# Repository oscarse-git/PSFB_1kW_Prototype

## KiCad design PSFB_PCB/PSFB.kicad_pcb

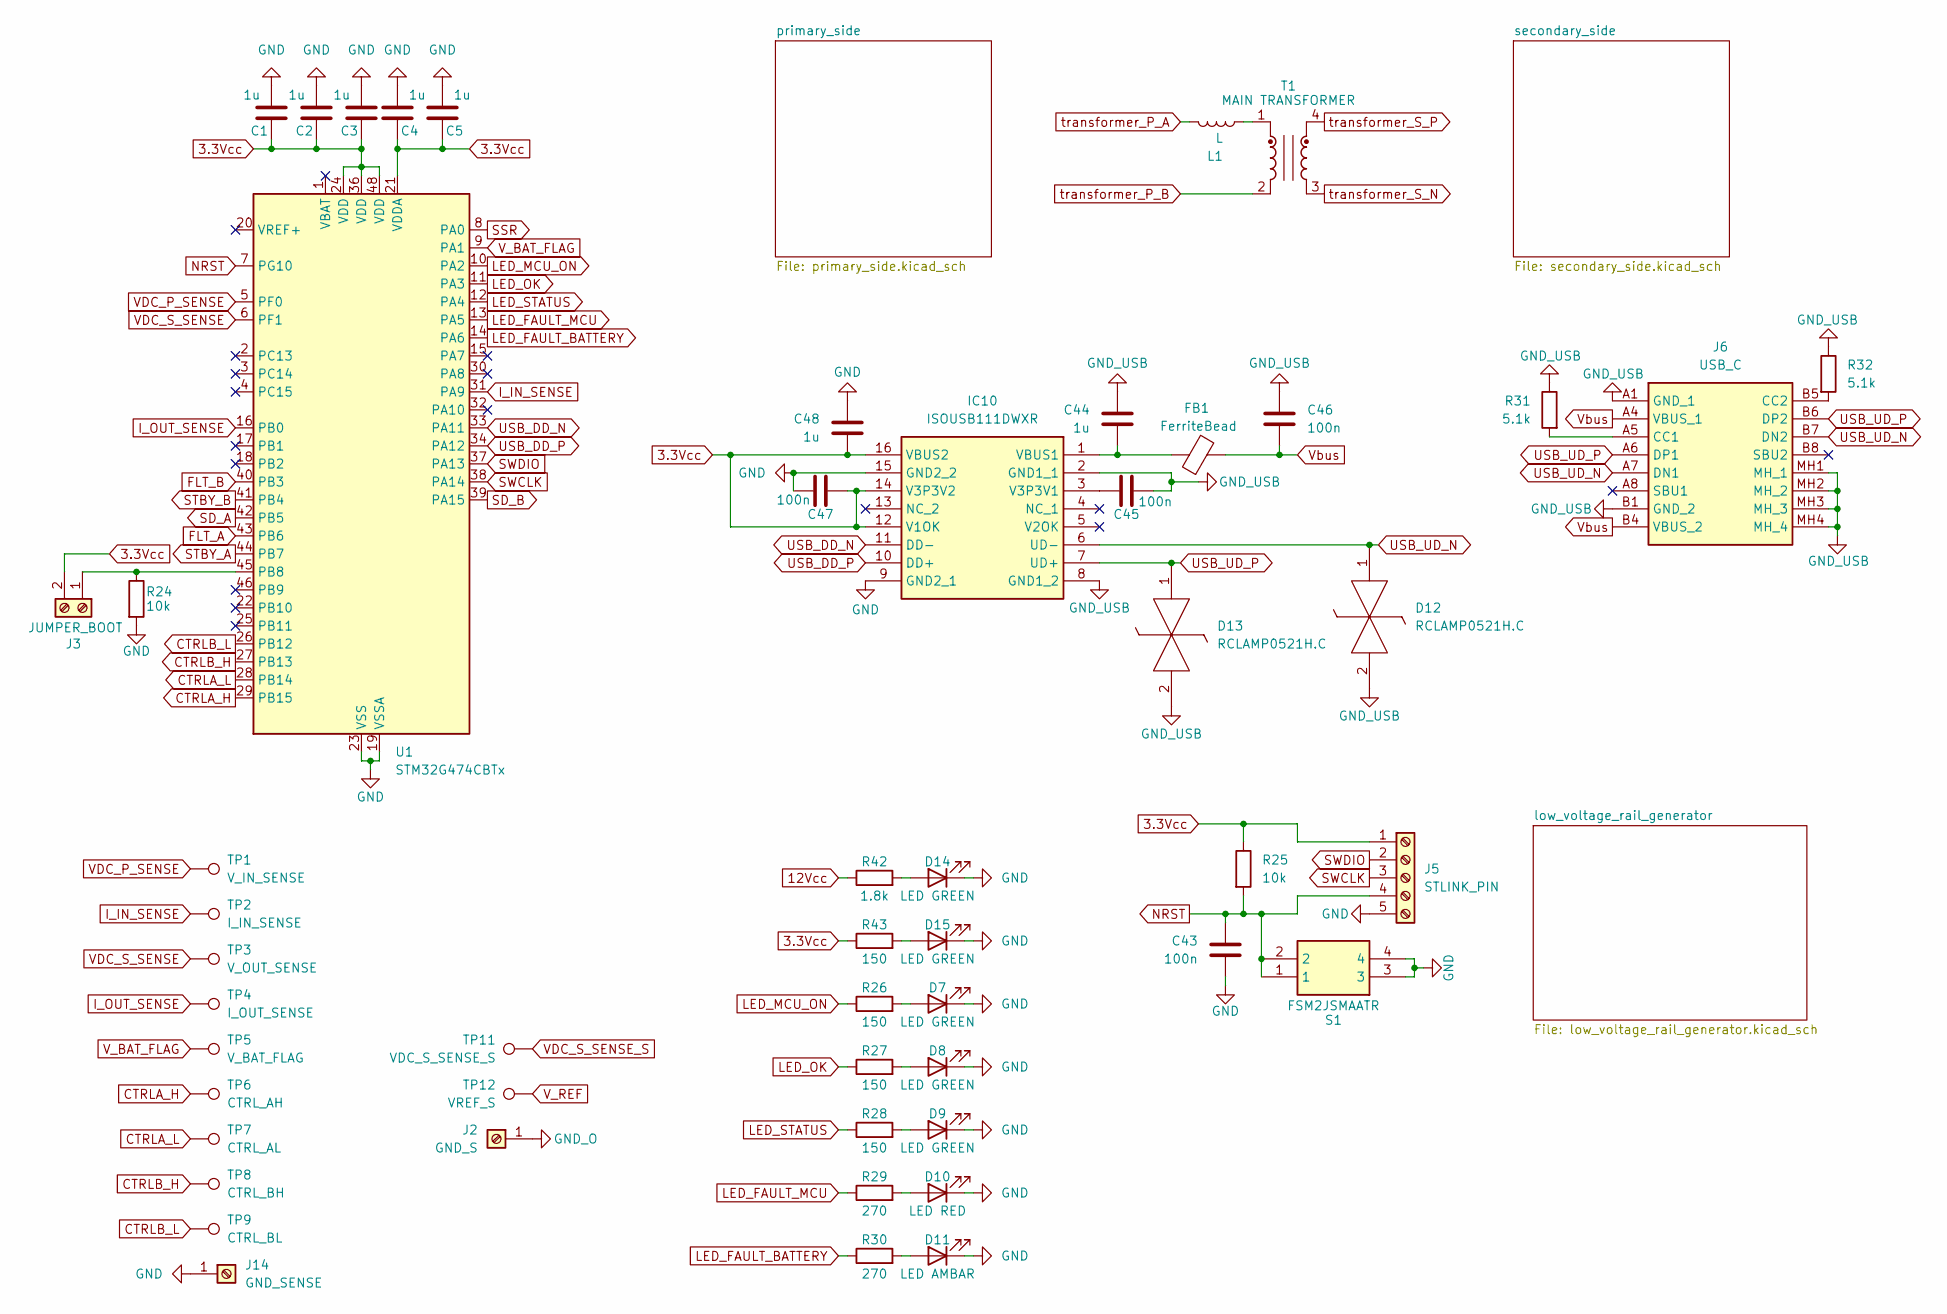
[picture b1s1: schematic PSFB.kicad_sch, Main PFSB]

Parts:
C1, C2, C3, C4, C5: 1u; C_0603_1608Metric_Pad1.08x0.95mm_HandSolder
C43, C45, C46, C47: 100n; C_1206_3216Metric_Pad1.33x1.80mm_HandSolder
C44, C48: 1u; C_1206_3216Metric
D7, D8, D9, D14, D15: LED GREEN; LED_0603_1608Metric
D10: LED RED; LED_1206_3216Metric_Pad1.42x1.75mm_HandSolder
D11: LED AMBAR; LED_1206_3216Metric_Pad1.42x1.75mm_HandSolder
D12, D13: RCLAMP0521H.C; SOD2513X120N; Mouser Part Number 947-RCLAMP0521H.C
FB1: FerriteBead; R_0603_1608Metric_Pad0.98x0.95mm_HandSolder
IC10: ISOUSB111DWXR; SOP65P1030X260-16N; Mouser Part Number 595-ISOUSB111DWXR
J2: GND_S; PinHeader_1x01_P2.54mm_Vertical
J3: JUMPER_BOOT; PinHeader_1x02_P2.54mm_Vertical
J5: STLINK_PIN; PinHeader_1x05_P2.54mm_Vertical
J6: USB_C; UJ20CHGMSMT4BP16TR; Manufacturer_Part_Number UJ20-C-H-G-MSMT-4B-P16-TR
J14: GND_SENSE; PinHeader_1x01_P2.54mm_Vertical
L1: L; L_Wurth_WE-HCFT-2012_LeadDiameter1.5mm
R24, R25: 10k; R_0603_1608Metric_Pad0.98x0.95mm_HandSolder
R26, R27, R28, R43: 150; R_0603_1608Metric_Pad0.98x0.95mm_HandSolder
R29, R30: 270; R_0603_1608Metric_Pad0.98x0.95mm_HandSolder
R31, R32: 5.1k; R_0603_1608Metric_Pad0.98x0.95mm_HandSolder
R42: 1.8k; R_0603_1608Metric_Pad0.98x0.95mm_HandSolder
S1: FSM2JSMAATR; FSM2J_1; Mouser Part Number 506-FSM2JSMAATR
T1: MAIN TRANSFORMER; TRANSFORMER_PQ_PSFB
TP1: V_IN_SENSE; TestPoint_Pad_D1.0mm
TP2: I_IN_SENSE; TestPoint_Pad_D1.0mm
TP3: V_OUT_SENSE; TestPoint_Pad_D1.0mm
TP4: I_OUT_SENSE; TestPoint_Pad_D1.0mm
TP5: V_BAT_FLAG; TestPoint_Pad_D1.0mm
TP6: CTRL_AH; TestPoint_Pad_D1.0mm
TP7: CTRL_AL; TestPoint_Pad_D1.0mm
TP8: CTRL_BH; TestPoint_Pad_D1.0mm
TP9: CTRL_BL; TestPoint_Pad_D1.0mm
TP11: VDC_S_SENSE_S; TestPoint_Pad_D1.0mm
TP12: VREF_S; TestPoint_Pad_D1.0mm
U1: STM32G474CBTx; LQFP-48_7x7mm_P0.5mm

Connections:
3.3Vcc: C1.1, C2.1, C3.1, C4.1, C5.1, C47.2, C48.2, IC10.12 (V1OK), IC10.14 (V3P3V2), IC10.16 (VBUS2), J3.2, J5.1, R25.1, R43.1, U1.21 (VDDA), U1.24 (VDD), U1.36 (VDD), U1.48 (VDD); also elsewhere on the board
12Vcc: R42.1; also elsewhere on the board
CTRLA_H: TP6.1, U1.29 (PB15); also elsewhere on the board
CTRLA_L: TP7.1, U1.28 (PB14); also elsewhere on the board
CTRLB_H: TP8.1, U1.27 (PB13); also elsewhere on the board
CTRLB_L: TP9.1, U1.26 (PB12); also elsewhere on the board
FLT_A: U1.43 (PB6); also elsewhere on the board
FLT_B: U1.40 (PB3); also elsewhere on the board
GND: C1.2, C2.2, C3.2, C4.2, C5.2, C43.2, C47.1, C48.1, D7.1 (K), D8.1 (K), D9.1 (K), D10.1 (K), D11.1 (K), D14.1 (K), D15.1 (K), IC10.9 (GND2_1), IC10.15 (GND2_2), J5.5, J14.1, R24.2, S1.3, S1.4, U1.19 (VSSA), U1.23 (VSS), U1.35 (VSS), U1.47 (VSS); also elsewhere on the board
GND_O: J2.1; also elsewhere on the board
GND_USB: C44.1, C45.1, C46.1, D12.2, D13.2, IC10.2 (GND1_1), IC10.8 (GND1_2), J6.A1 (GND_1), J6.B1 (GND_2), J6.MH1 (MH_1), J6.MH2 (MH_2), J6.MH3 (MH_3), J6.MH4 (MH_4), R31.1, R32.1
I_IN_SENSE: TP2.1, U1.31 (PA9); also elsewhere on the board
I_OUT_SENSE: TP4.1, U1.16 (PB0); also elsewhere on the board
LED_FAULT_BATTERY: R30.1, U1.14 (PA6)
LED_FAULT_MCU: R29.1, U1.13 (PA5)
LED_MCU_ON: R26.1, U1.10 (PA2)
LED_OK: R27.1, U1.11 (PA3)
LED_STATUS: R28.1, U1.12 (PA4)
NRST: C43.1, J5.4, R25.2, S1.1, S1.2, U1.7 (PG10)
unnamed: D7.2 (A), R26.2
unnamed: D8.2 (A), R27.2
unnamed: D9.2 (A), R28.2
unnamed: D10.2 (A), R29.2
unnamed: D11.2 (A), R30.2
unnamed: D14.2 (A), R42.2
unnamed: D15.2 (A), R43.2
unnamed: C45.2, IC10.3 (V3P3V1)
unnamed: C44.2, FB1.1, IC10.1 (VBUS1)
unnamed: J3.1, R24.1, U1.45 (PB8)
unnamed: J6.A5 (CC1), R31.2
unnamed: J6.B5 (CC2), R32.2
unnamed: L1.2, T1.1
SD_A: U1.42 (PB5); also elsewhere on the board
SD_B: U1.39 (PA15); also elsewhere on the board
SSR: U1.8 (PA0); also elsewhere on the board
STBY_A: U1.44 (PB7); also elsewhere on the board
STBY_B: U1.41 (PB4); also elsewhere on the board
SWCLK: J5.3, U1.38 (PA14)
SWDIO: J5.2, U1.37 (PA13)
USB_DD_N: IC10.11 (DD-), U1.33 (PA11)
USB_DD_P: IC10.10 (DD+), U1.34 (PA12)
USB_UD_N: D12.1, IC10.6 (UD-), J6.A7 (DN1), J6.B7 (DN2)
USB_UD_P: D13.1, IC10.7 (UD+), J6.A6 (DP1), J6.B6 (DP2)
VDC_P_SENSE: TP1.1, U1.5 (PF0); also elsewhere on the board
VDC_S_SENSE: TP3.1, U1.6 (PF1); also elsewhere on the board
VDC_S_SENSE_S: TP11.1; also elsewhere on the board
V_BAT_FLAG: TP5.1, U1.9 (PA1); also elsewhere on the board
V_REF: TP12.1; also elsewhere on the board
Vbus: C46.2, FB1.2, J6.A4 (VBUS_1), J6.B4 (VBUS_2)
transformer_P_A: L1.1; also elsewhere on the board
transformer_P_B: T1.2; also elsewhere on the board
transformer_S_N: T1.3; also elsewhere on the board
transformer_S_P: T1.4; also elsewhere on the board

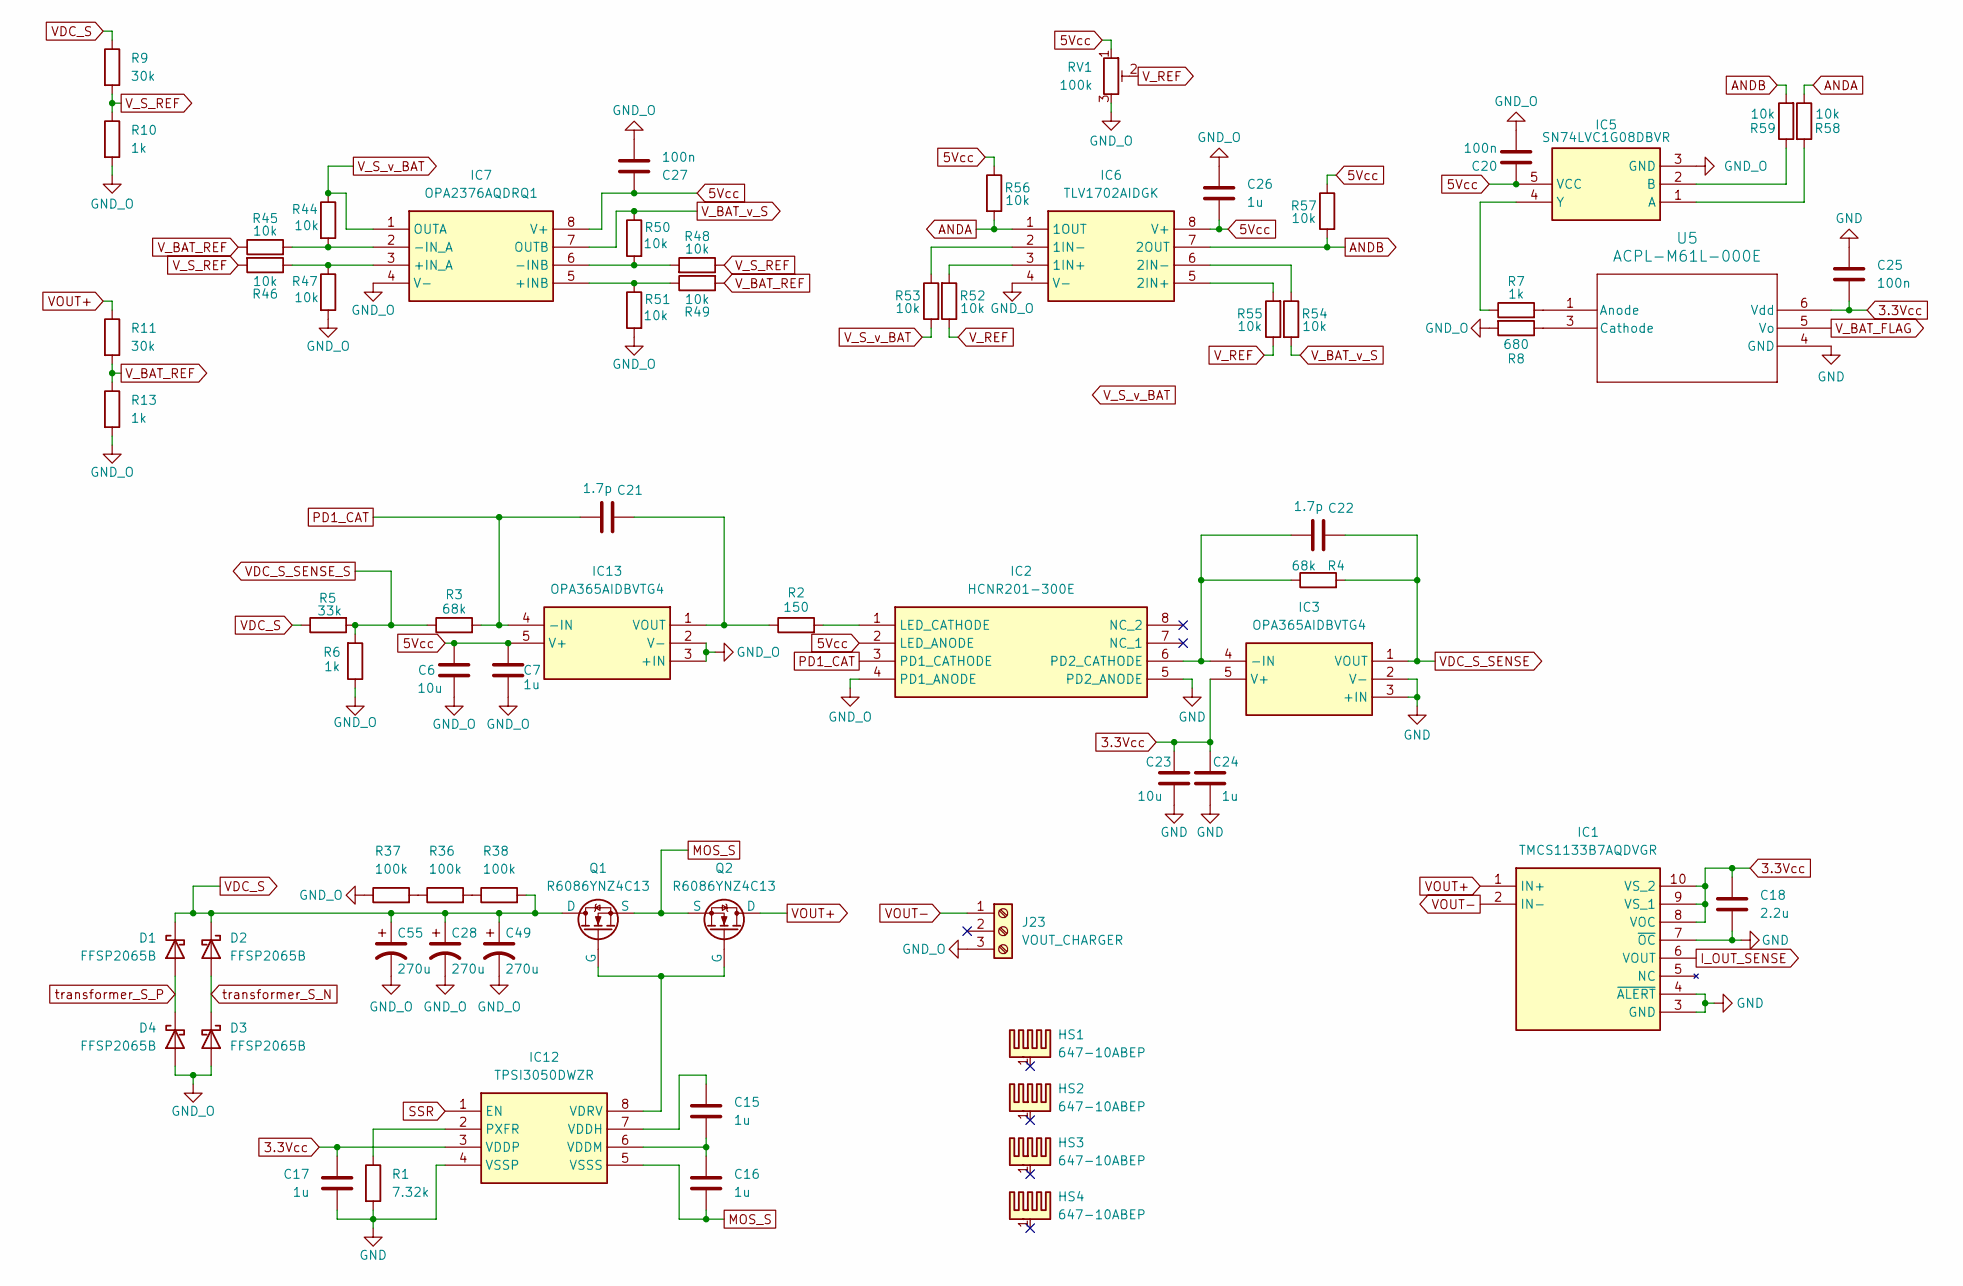
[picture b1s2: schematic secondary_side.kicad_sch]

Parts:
C6, C23: 10u; C_1206_3216Metric
C7, C15, C16, C17, C24, C26: 1u; C_1206_3216Metric
C18: 2.2u; C_0603_1608Metric_Pad1.08x0.95mm_HandSolder
C20, C25, C27: 100n; C_1206_3216Metric_Pad1.33x1.80mm_HandSolder
C21, C22: 1.7p; C_0603_1608Metric_Pad1.08x0.95mm_HandSolder
C28, C49, C55: 270u; CP_Radial_D25.0mm_P10.00mm_SnapIn
D1, D2, D3, D4: FFSP2065B; TO-220-2_Vertical
HS1, HS2, HS3, HS4: 647-10ABEP; XSD-C4649_TO220_Heatsink
IC1: TMCS1133B7AQDVGR; Manufacturer_Part_Number TMCS1133B7AQDVGR
IC2: HCNR201-300E; HCNR201300E; Mouser Part Number 630-HCNR201-300E
IC3, IC13: OPA365AIDBVTG4; SOT95P280X145-5N; Mouser Part Number 595-OPA365AIDBVTG4
IC5: SN74LVC1G08DBVR; SOT95P280X145-5N; Mouser Part Number 595-SN74LVC1G08DBVR
IC6: TLV1702AIDGK; SOP65P490X110-8N; Mouser Part Number 595-TLV1702AIDGK
IC7: OPA2376AQDRQ1; SOIC127P600X175-8N; Mouser Part Number 595-OPA2376AQDRQ1
IC12: TPSI3050DWZR; SOIC127P1150X280-8N; Mouser Part Number 595-TPSI3050DWZR
J23: VOUT_CHARGER; 1731734
Q1, Q2: R6086YNZ4C13; TO-247-3_Vertical
R1: 7.32k; R_0603_1608Metric_Pad0.98x0.95mm_HandSolder
R2: 150; R_0805_2012Metric_Pad1.20x1.40mm_HandSolder
R3, R4: 68k; R_0805_2012Metric_Pad1.20x1.40mm_HandSolder
R5: 33k; R_0603_1608Metric_Pad0.98x0.95mm_HandSolder
R6, R7, R10, R13: 1k; R_0603_1608Metric_Pad0.98x0.95mm_HandSolder
R8: 680; R_0603_1608Metric_Pad0.98x0.95mm_HandSolder
R9, R11: 30k; R_0603_1608Metric_Pad0.98x0.95mm_HandSolder
R36, R37, R38: 100k; R_1206_3216Metric_Pad1.30x1.75mm_HandSolder
R44, R45, R46, R47, R48, R49, R50, R51, R52, R53, R54, R55, R56, R57, R58, R59: 10k; R_0603_1608Metric_Pad0.98x0.95mm_HandSolder
RV1: 100k; PVG3A104C01R00
U5: ACPL-M61L-000E; SO-5_AVA-L

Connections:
3.3Vcc: C17.1, C18.1, C23.1, C24.1, C25.2, IC1.8 (VOC), IC1.9 (VS_1), IC1.10 (VS_2), IC3.5 (V+), IC12.3 (VDDP), U5.6 (Vdd); also elsewhere on the board
5Vcc: C6.1, C7.1, C20.1, C26.2, C27.1, IC2.2 (LED_ANODE), IC5.5 (VCC), IC6.8 (V+), IC7.8 (V+), IC13.5 (V+), R56.1, R57.1, RV1.1; also elsewhere on the board
ANDA: IC6.1 (1OUT), R56.2, R58.1
ANDB: IC6.7 (2OUT), R57.2, R59.2
GND: C17.2, C18.2, C23.2, C24.2, C25.1, IC1.3 (GND), IC1.4 (~ALERT), IC1.7 (~OC), IC2.5 (PD2_ANODE), IC3.2 (V-), IC3.3 (+IN), IC12.4 (VSSP), R1.2, U5.4 (GND); also elsewhere on the board
GND_O: C6.2, C7.2, C20.2, C26.1, C27.2, C28.2, C49.2, C55.2, D3.2 (A), D4.2 (A), IC2.4 (PD1_ANODE), IC5.3 (GND), IC6.4 (V-), IC7.4 (V-), IC13.2 (V-), IC13.3 (+IN), J23.3, R6.1, R8.2, R10.2, R13.2, R37.1, R47.2, R51.2, RV1.3; also elsewhere on the board
I_OUT_SENSE: IC1.6 (VOUT); also elsewhere on the board
MOS_S: C16.2, IC12.5 (VSSS), Q1.3 (S), Q2.3 (S)
unnamed: IC2.1 (LED_CATHODE), R2.2
unnamed: C22.2, IC2.6 (PD2_CATHODE), IC3.4 (-IN), R4.1
unnamed: IC5.1 (A), R58.2
unnamed: IC5.2 (B), R59.1
unnamed: IC5.4 (Y), R7.1
unnamed: IC6.3 (1IN+), R52.2
unnamed: IC6.2 (1IN-), R53.1
unnamed: IC6.5 (2IN+), R55.2
unnamed: IC6.6 (2IN-), R54.1
unnamed: IC7.5 (+INB), R49.1, R51.1
unnamed: IC7.3 (+IN_A), R46.1, R47.1
unnamed: IC7.6 (-INB), R48.2, R50.2
unnamed: IC7.2 (-IN_A), R44.2, R45.2
unnamed: IC12.2 (PXFR), R1.1
unnamed: C15.1, IC12.7 (VDDH)
unnamed: C15.2, C16.1, IC12.6 (VDDM)
unnamed: IC12.8 (VDRV), Q1.2 (G), Q2.2 (G)
unnamed: C21.1, IC13.1 (VOUT), R2.1
unnamed: R36.1, R37.2
unnamed: R36.2, R38.1
unnamed: R7.2, U5.1 (Anode)
unnamed: R8.1, U5.3 (Cathode)
PD1_CAT: C21.2, IC2.3 (PD1_CATHODE), IC13.4 (-IN), R3.2
SSR: IC12.1 (EN); also elsewhere on the board
VDC_S: C28.1, C49.1, C55.1, D1.1 (K), D2.1 (K), Q1.1 (D), R5.1, R9.1, R38.2
VDC_S_SENSE: C22.1, IC3.1 (VOUT), R4.2; also elsewhere on the board
VDC_S_SENSE_S: R3.1, R5.2, R6.2; also elsewhere on the board
VOUT+: IC1.1 (IN+), Q2.1 (D), R11.1
VOUT-: IC1.2 (IN-), J23.1
V_BAT_FLAG: U5.5 (Vo); also elsewhere on the board
V_BAT_REF: R11.2, R13.1, R45.1, R49.2
V_BAT_v_S: IC7.7 (OUTB), R50.1, R54.2
V_REF: R52.1, R55.1, RV1.2; also elsewhere on the board
V_S_REF: R9.2, R10.1, R46.2, R48.1
V_S_v_BAT: IC7.1 (OUTA), R44.1, R53.2
transformer_S_N: D2.2 (A), D3.1 (K); also elsewhere on the board
transformer_S_P: D1.2 (A), D4.1 (K); also elsewhere on the board

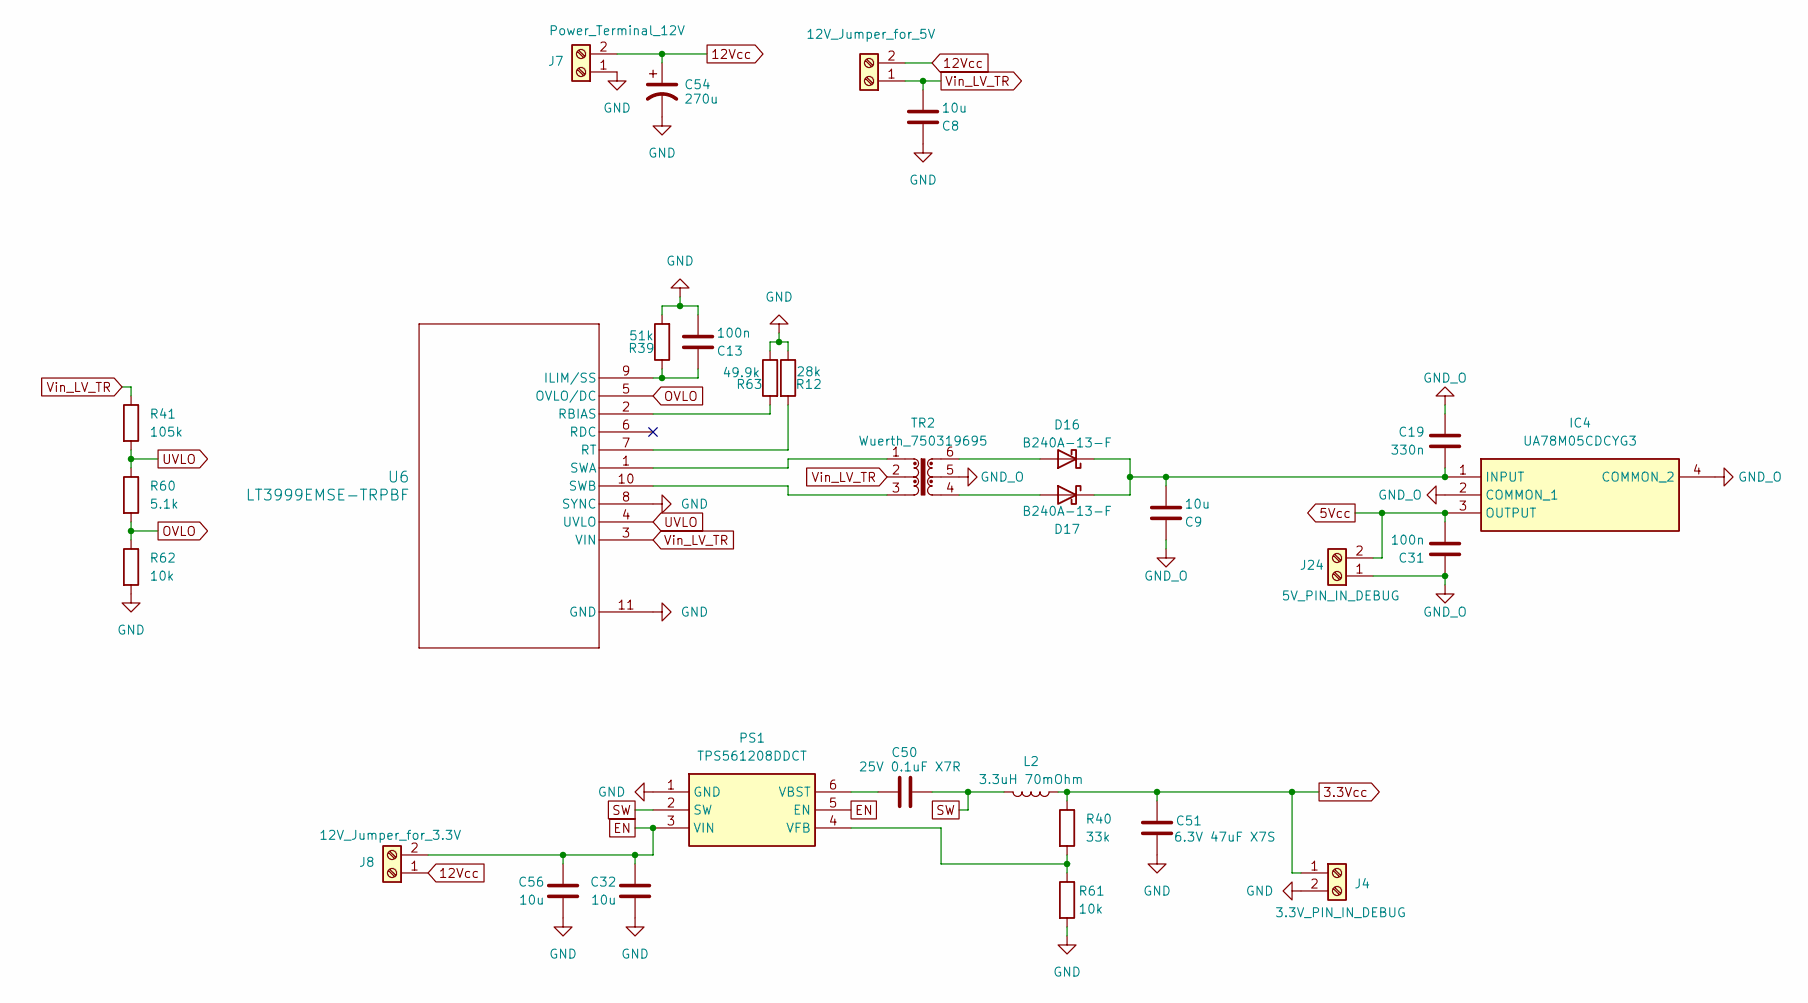
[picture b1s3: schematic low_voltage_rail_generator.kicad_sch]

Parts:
C8, C9, C32, C56: 10u; C_1206_3216Metric
C13, C31: 100n; C_1206_3216Metric_Pad1.33x1.80mm_HandSolder
C19: 330n; C_1206_3216Metric_Pad1.33x1.80mm_HandSolder
C50: 25V 0.1uF X7R; C_0805_2012Metric_Pad1.18x1.45mm_HandSolder
C51: 6.3V 47uF X7S; C_1210_3225Metric_Pad1.33x2.70mm_HandSolder
C54: 270u; CP_Radial_D25.0mm_P10.00mm_SnapIn
D16, D17: B240A-13-F; D_SMA
IC4: UA78M05CDCYG3; SOT230P700X180-4N; Mouser Part Number 595-UA78M05CDCYG3
J1: 12V_Jumper_for_5V; PinHeader_1x02_P2.54mm_Vertical
J4: 3.3V_PIN_IN_DEBUG; PinHeader_1x02_P2.54mm_Vertical
J7: Power_Terminal_12V; 15465512
J8: 12V_Jumper_for_3.3V; PinHeader_1x02_P2.54mm_Vertical
J24: 5V_PIN_IN_DEBUG; PinHeader_1x02_P2.54mm_Vertical
L2: 3.3uH 70mOhm; 784777033
PS1: TPS561208DDCT; SOT95P280X110-6N; Mouser Part Number 595-TPS561208DDCT
R12: 28k; R_0603_1608Metric_Pad0.98x0.95mm_HandSolder
R39: 51k; R_1206_3216Metric_Pad1.30x1.75mm_HandSolder
R40: 33k; R_0603_1608Metric_Pad0.98x0.95mm_HandSolder
R41: 105k; R_1206_3216Metric_Pad1.30x1.75mm_HandSolder
R60: 5.1k; R_1206_3216Metric_Pad1.30x1.75mm_HandSolder
R61: 10k; R_0603_1608Metric_Pad0.98x0.95mm_HandSolder
R62: 10k; R_1206_3216Metric_Pad1.30x1.75mm_HandSolder
R63: 49.9k; R_0603_1608Metric_Pad0.98x0.95mm_HandSolder
TR2: Wuerth_750319695; 750319690
U6: LT3999EMSE-TRPBF; MSOP-10_MSE_LIT-L

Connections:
3.3Vcc: C51.1, J4.1, L2.1, R40.1; also elsewhere on the board
5Vcc: C31.2, IC4.3 (OUTPUT), J24.2; also elsewhere on the board
12Vcc: C54.1, J1.2, J7.2, J8.1; also elsewhere on the board
EN: C32.1, C56.1, J8.2, PS1.3 (VIN), PS1.5 (EN)
GND: C8.1, C13.2, C32.2, C51.2, C54.2, C56.2, J4.2, J7.1, PS1.1 (GND), R12.1, R39.2, R61.2, R62.2, R63.1, U6.8 (SYNC), U6.11 (GND); also elsewhere on the board
GND_O: C9.1, C19.1, C31.1, IC4.2 (COMMON_1), IC4.4 (COMMON_2), J24.1, TR2.5; also elsewhere on the board
unnamed: D16.2 (A), TR2.6
unnamed: C9.2, C19.2, D16.1 (K), D17.1 (K), IC4.1 (INPUT)
unnamed: D17.2 (A), TR2.4
unnamed: C50.2, PS1.6 (VBST)
unnamed: PS1.4 (VFB), R40.2, R61.1
unnamed: C13.1, R39.1, U6.9 (ILIM/SS)
unnamed: R63.2, U6.2 (RBIAS)
unnamed: R12.2, U6.7 (RT)
unnamed: TR2.1, U6.1 (SWA)
unnamed: TR2.3, U6.10 (SWB)
OVLO: R60.2, R62.1, U6.5 (OVLO/DC)
SW: C50.1, L2.2, PS1.2 (SW)
UVLO: R41.2, R60.1, U6.4 (UVLO)
Vin_LV_TR: C8.2, J1.1, R41.1, TR2.2, U6.3 (VIN)

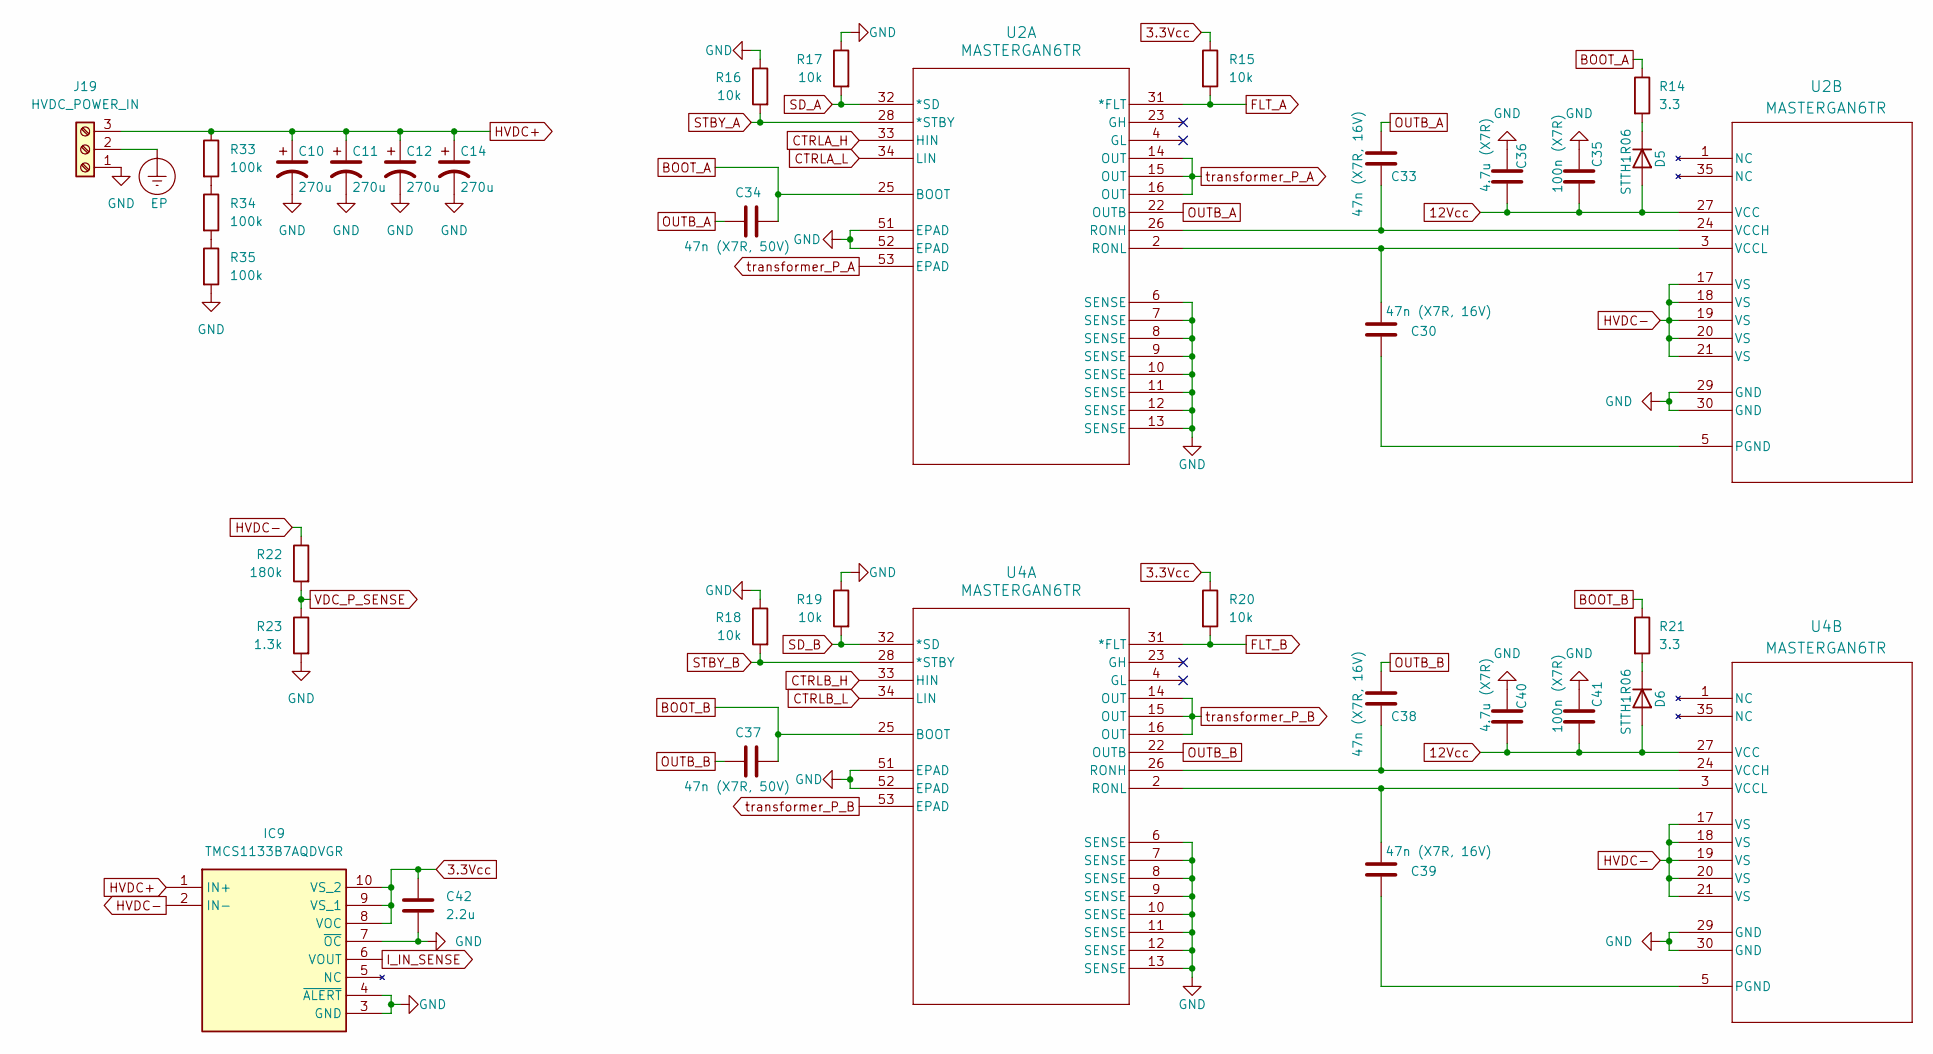
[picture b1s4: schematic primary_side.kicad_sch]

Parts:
C10, C11, C12, C14: 270u; CP_Radial_D25.0mm_P10.00mm_SnapIn
C30, C33, C38, C39: 47n (X7R, 16V); C_0402_1005Metric
C34, C37: 47n (X7R, 50V); C_0603_1608Metric
C35, C41: 100n (X7R); C_0603_1608Metric_Pad1.08x0.95mm_HandSolder
C36, C40: 4.7u (X7R); C_1206_3216Metric_Pad1.33x1.80mm_HandSolder
C42: 2.2u; C_0603_1608Metric_Pad1.08x0.95mm_HandSolder
D5, D6: STTH1R06; DIOM5126X265N
IC9: TMCS1133B7AQDVGR; Manufacturer_Part_Number TMCS1133B7AQDVGR
J19: HVDC_POWER_IN; 1731734
R14, R21: 3.3; R_0805_2012Metric_Pad1.20x1.40mm_HandSolder
R15, R16, R17, R18, R19, R20: 10k; R_0603_1608Metric_Pad0.98x0.95mm_HandSolder
R22: 180k; R_1206_3216Metric_Pad1.30x1.75mm_HandSolder
R23: 1.3k; R_1206_3216Metric_Pad1.30x1.75mm_HandSolder
R33, R34, R35: 100k; R_1206_3216Metric_Pad1.30x1.75mm_HandSolder
U2, U4: MASTERGAN6TR; QFN35_9X9_STM-M

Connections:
3.3Vcc: C42.1, IC9.8 (VOC), IC9.9 (VS_1), IC9.10 (VS_2), R15.1, R20.1; also elsewhere on the board
12Vcc: C35.2, C36.2, C40.2, C41.2, D5.2 (A), D6.2 (A), U2.27 (VCC), U4.27 (VCC); also elsewhere on the board
BOOT_A: C34.2, R14.1, U2.25 (BOOT)
BOOT_B: C37.2, R21.1, U4.25 (BOOT)
CTRLA_H: U2.33 (HIN); also elsewhere on the board
CTRLA_L: U2.34 (LIN); also elsewhere on the board
CTRLB_H: U4.33 (HIN); also elsewhere on the board
CTRLB_L: U4.34 (LIN); also elsewhere on the board
EP: J19.2
FLT_A: R15.2, U2.31 (*FLT); also elsewhere on the board
FLT_B: R20.2, U4.31 (*FLT); also elsewhere on the board
GND: C10.2, C11.2, C12.2, C14.2, C35.1, C36.1, C40.1, C41.1, C42.2, IC9.3 (GND), IC9.4 (~ALERT), IC9.7 (~OC), J19.1, R16.1, R17.1, R18.1, R19.1, R23.2, R35.2, U2.6 (SENSE), U2.7 (SENSE), U2.8 (SENSE), U2.9 (SENSE), U2.10 (SENSE), U2.11 (SENSE), U2.12 (SENSE), U2.13 (SENSE), U2.29 (GND), U2.30 (GND), U2.51 (EPAD), U2.52 (EPAD), U4.6 (SENSE), U4.7 (SENSE), U4.8 (SENSE), U4.9 (SENSE), U4.10 (SENSE), U4.11 (SENSE), U4.12 (SENSE), U4.13 (SENSE), U4.29 (GND), U4.30 (GND), U4.51 (EPAD), U4.52 (EPAD); also elsewhere on the board
HVDC+: C10.1, C11.1, C12.1, C14.1, IC9.1 (IN+), J19.3, R33.1
HVDC-: IC9.2 (IN-), R22.1, U2.17 (VS), U2.18 (VS), U2.19 (VS), U2.20 (VS), U2.21 (VS), U4.17 (VS), U4.18 (VS), U4.19 (VS), U4.20 (VS), U4.21 (VS)
I_IN_SENSE: IC9.6 (VOUT); also elsewhere on the board
unnamed: D5.1 (K), R14.2
unnamed: D6.1 (K), R21.2
unnamed: R33.2, R34.1
unnamed: R34.2, R35.1
unnamed: C33.2, U2.24 (VCCH), U2.26 (RONH)
unnamed: C30.1, U2.2 (RONL), U2.3 (VCCL)
unnamed: C30.2, U2.5 (PGND)
unnamed: C38.2, U4.24 (VCCH), U4.26 (RONH)
unnamed: C39.1, U4.2 (RONL), U4.3 (VCCL)
unnamed: C39.2, U4.5 (PGND)
OUTB_A: C33.1, C34.1, U2.22 (OUTB)
OUTB_B: C37.1, C38.1, U4.22 (OUTB)
SD_A: R17.2, U2.32 (*SD); also elsewhere on the board
SD_B: R19.2, U4.32 (*SD); also elsewhere on the board
STBY_A: R16.2, U2.28 (*STBY); also elsewhere on the board
STBY_B: R18.2, U4.28 (*STBY); also elsewhere on the board
VDC_P_SENSE: R22.2, R23.1; also elsewhere on the board
transformer_P_A: U2.14 (OUT), U2.15 (OUT), U2.16 (OUT), U2.53 (EPAD); also elsewhere on the board
transformer_P_B: U4.14 (OUT), U4.15 (OUT), U4.16 (OUT), U4.53 (EPAD); also elsewhere on the board

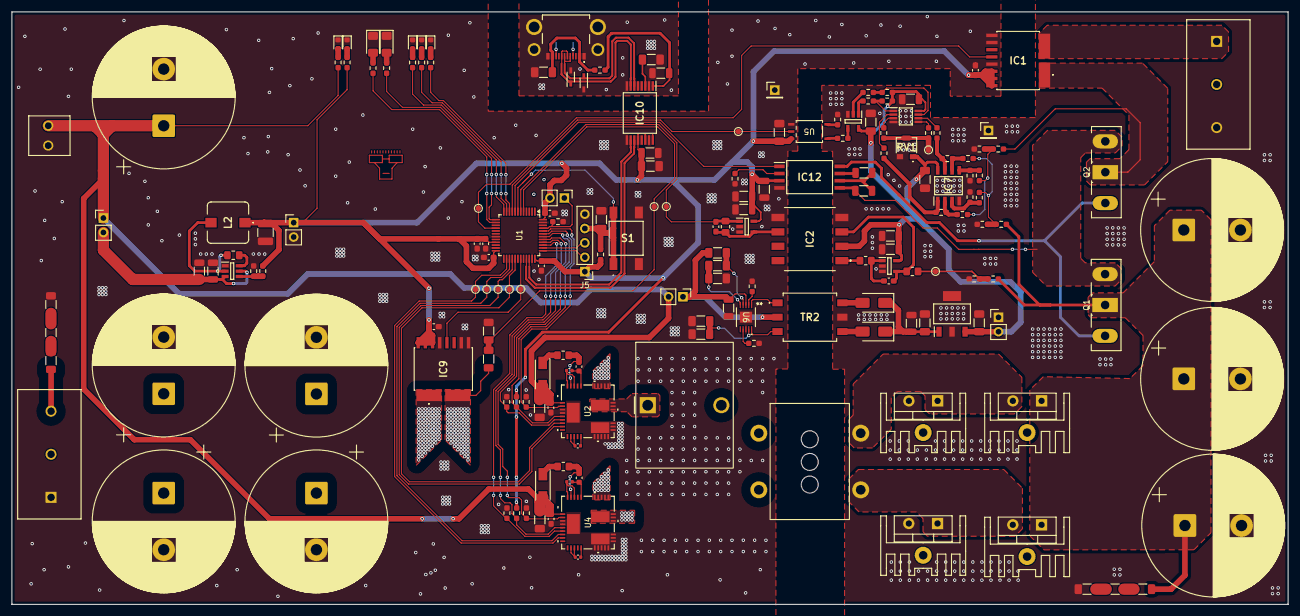
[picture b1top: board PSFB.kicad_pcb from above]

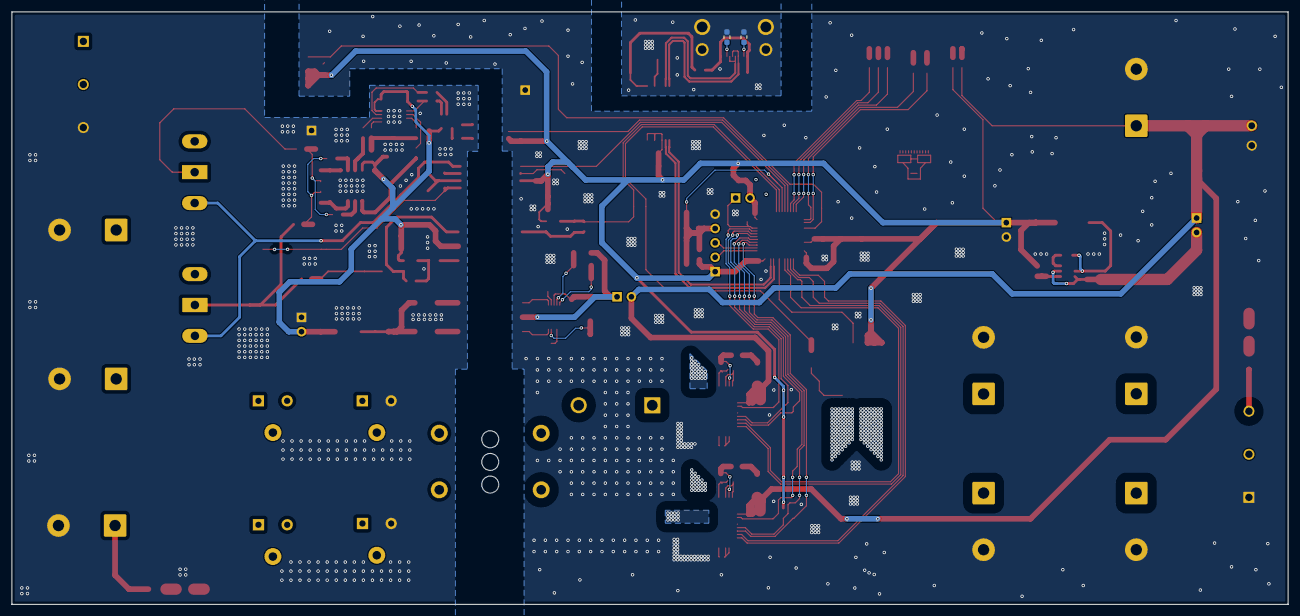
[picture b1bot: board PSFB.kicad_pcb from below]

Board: 4 copper layers, 225.4 x 104.7 mm, 186 parts (2 on the bottom side), 118 nets.
